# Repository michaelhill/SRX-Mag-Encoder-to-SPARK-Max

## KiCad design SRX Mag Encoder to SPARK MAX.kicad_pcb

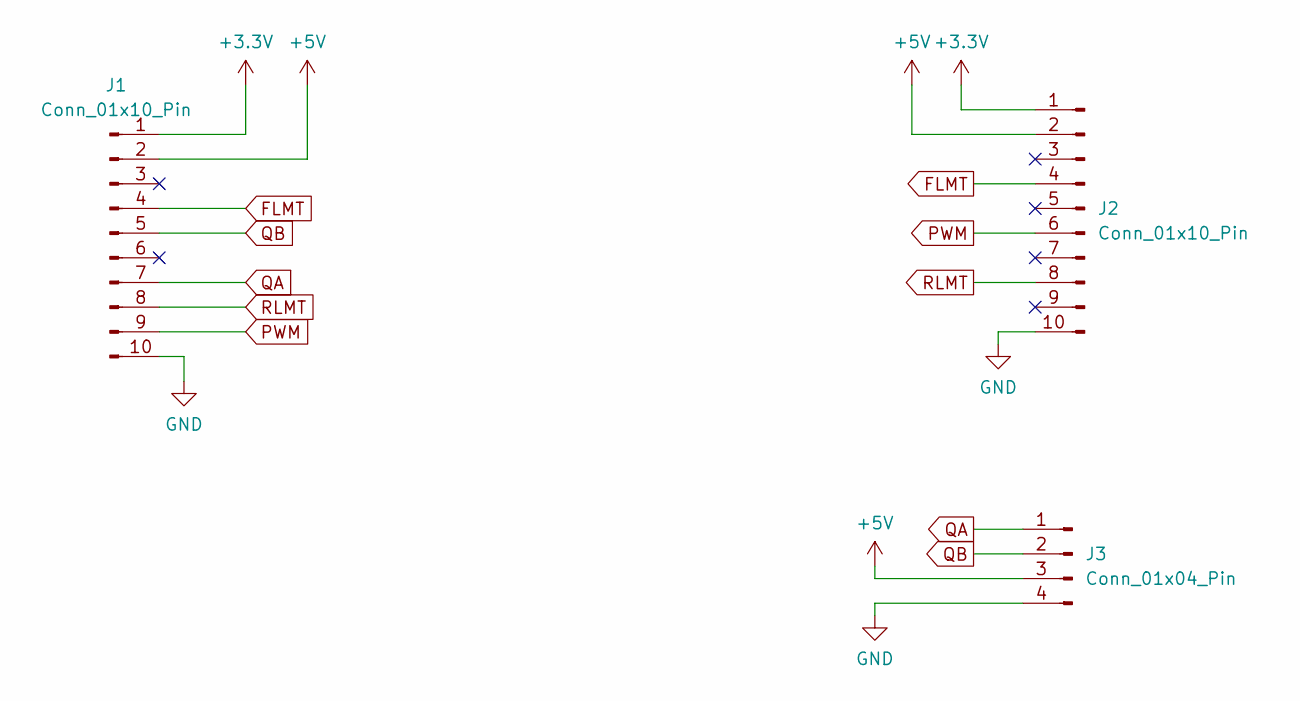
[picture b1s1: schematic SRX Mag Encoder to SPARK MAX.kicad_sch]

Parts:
J1: Conn_01x10_Pin; 3220-10-0300-00
J2: Conn_01x10_Pin; CONN10_M50-3120545_HRW
J3: Conn_01x04_Pin

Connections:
+3.3V: J1.1, J2.1
+5V: J1.2, J2.2, J3.3
FLMT: J1.4, J2.4
GND: J1.10, J2.10, J3.4
PWM: J1.9, J2.6
QA: J1.7, J3.1
QB: J1.5, J3.2
RLMT: J1.8, J2.8

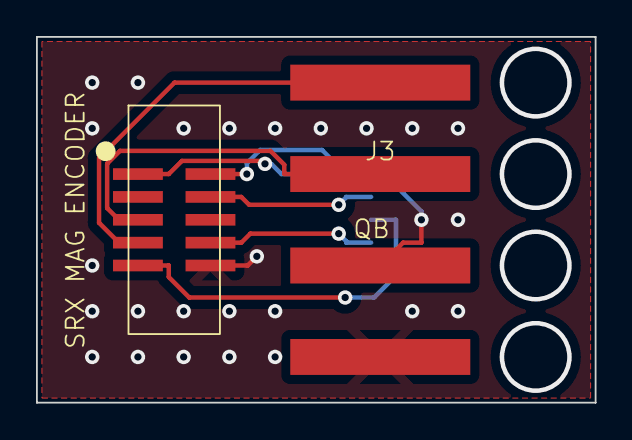
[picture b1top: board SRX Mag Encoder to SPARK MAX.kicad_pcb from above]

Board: 2 copper layers, 31.0 x 20.3 mm, 3 parts (1 on the bottom side), 8 nets.

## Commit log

2023-12-31 first rev
2023-12-31 clean up
2024-01-03 Routed power outputs to solder pads for roborio connection
